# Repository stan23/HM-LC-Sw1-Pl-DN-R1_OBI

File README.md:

# HM-LC-Sw1-Pl-DN-R1_OBI          

Umbau [OBI-Wifi-Stecker](https://www.obi.de/hausfunksteuerung/wifi-stecker-schuko/p/2291706) zu HM-LC-Sw1-Pl-DN-R1_OBI

Dies basiert auf der hervorragenden Arbeit von [pa-pa](https://github.com/pa-pa/AskSinPP),  [Jérôme](https://github.com/jp112sdl/Beispiel_AskSinPP) und micha68.

# Hardware

### Bauteile

#### Reichelt

[Bestellliste](https://www.reichelt.de/my/1496083)

Bauteil                  | Bestellnummer   | Anzahl | Kommentar
------------------------ | --------------- | ------ | ---------
C6                       | X5R-G0603 10/6  |   1    | -
C1, C2, C3, C8           | X7R-G0603 100N  |   4    | -
R1                       | RND 0603 1 10K  |   1    | -
U1                       | ATMEGA 328P-AU  |   1    | -
Verbinder zu U2          | SL 1X20G 2,00   |   1    | optional, hilfreich zum Anschließen des ISP
Verbinder zu U2          | MPE 156-1-032   |   1    | optional

#### Sonstiges

Bauteil | Bestellnummer            | Anzahl | Kommentar
------- | ------------------------ | ------ | ---------
U2      | CC1101 Funkmodul 868 MHz |   1    | z.B. [eBay](https://www.ebay.de/itm/272455136087)

~8,3 cm Draht als Antenne

### Programmieradapter
- 1x ISP (um den Bootloader zu brennen, z.B. [diesen hier](https://www.diamex.de/dxshop/USB-ISP-Programmer-fuer-Atmel-AVR-Rev2))
- 1x FTDI Adapter (z.B. [Amazon](https://www.amazon.de/FT232RL-FTDI-USB-auf-TTL-Serienadapter-Arduino/dp/B00HSXDGOE))

# Software

### Fuses
Ext:  0xFF
High: 0xD2
Low:  0xE2

`C:\Program Files (x86)\Arduino\hardware\tools\avr\bin> .\avrdude -C ..\etc\avrdude.conf -p m328p -P com7 -c stk500v2 -U lfuse:w:0xE2:m -U hfuse:w:0xD2:m -U efuse:w:0xFF:m`

### Bootloader

Aus der Arduino IDE, für ATmega328P (3,3 V, 8 MHz):

`C:\Program Files (x86)\Arduino\hardware\tools\avr\bin> .\avrdude -C ..\etc\avrdude.conf -p m328p -P com7 -c stk500v2 -U flash:w:..\..\..\arduino\avr\bootloaders\atmega\ATmegaBOOT_168_atmega328_pro_8MHz.hex`

### Firmware

https://github.com/jp112sdl/Beispiel_AskSinPP/tree/master/examples/HM-LC-Sw1-Pl-DN-R1_OBI

Benötigt wird die AskSinPP aus dem master-Branch, der V3-Branch ist zu alt.

# Bauanleitung

Zuerst den ATmega auflöten, die Markierung (kleiner Punkt) muss zur Beschriftung U1 zeigen.
Danach die Kondensatoren und den Widerstand auflöten.

Mit einem Multimeter messen ob kein Kurzschluss zwischen VCC und GND besteht (mehrere 10 K Widerstand sind okay).

Den ISP Programmieradapter an die Lötaugen des CC1101 anschließen. Ein Adapterkabel vom 6-poligen ISP-Adapter auf eine 2 mm-Stiftleiste wird empfohlen :)

Pin am ISP-Kabel | Bedeutung
---------------- | ----------
1                | MISO
2                | VCC
3                | SCK
4                | MOSI
5                | Reset
6                | GND

Über den ISP den Bootloader (ATmegaBOOT_168_atmega328_pro_8MHz.hex) der mit der Arduino IDE mitgeliefert wird, brennen und die Fuses setzen. Dabei muss die Platine mit 3,3 V oder 5 V versorgt werden, entweder vom ISP oder vom FTDI-Adapter. So lange das CC1101 nicht bestückt ist, sind 5 V kein Problem.

*Achtung*: nicht die default Fuses der Arduino IDE brennen, sonst startet der ATmega nicht mehr weil er einen externen Oszillator erwartet!

Danach den FTDI USB-seriell-Adapter an die 2,54 mm-Stiftleiste stecken und mit der Arduino IDE den Sketch flashen.

Anschließend kann das Funkmodul auf der Rückseite aufgelötet werden. Dabei gibt es verschiedene Möglichkeiten:
- mit Stift- und Buchsenleiste (abnehmbar)
- mit Stiftleiste
- flach auf die SMD-Pads, hier empfiehlt es sich die Lötaugen des CC1101 zur Hälfte abzufeilen

An den Antennenanschluss muss noch das 8,3 cm Drahtstück angelötet werden.

Jetzt wieder den FTDI USB-seriell-Adapter an die 2,54 mm-Stiftleiste stecken und mit einem Terminalprogramm die Ausgabe beobachten. Es sollten schon *Ignore...*-Meldungen empfangen und angezeigt werden.

Als nächstes muss das überflüssige WLAN-Modul aus dem OBI-Stecker ausgelötet und die neue Platine eingelötet werden. Der Antennendraht muss mit Heißkleber im Gehäuse befestigt werden, so dass er möglichst weit von 230 V entfernt ist!

Nach dem Zusammenbau kann der Anlernvorgang durch langes Drücken der einzigen Taste gestartet werden. Die Anlernprozedur wird durch langsames Blinken der blauen WLAN-LED angezeigt, der Erfolg durch schnelles Blinken.

# Bilder

Dieses Werk ist lizenziert unter einer [Creative Commons Namensnennung - Nicht-kommerziell - Weitergabe unter gleichen Bedingungen 4.0 International Lizenz](http://creativecommons.org/licenses/by-nc-sa/4.0/).

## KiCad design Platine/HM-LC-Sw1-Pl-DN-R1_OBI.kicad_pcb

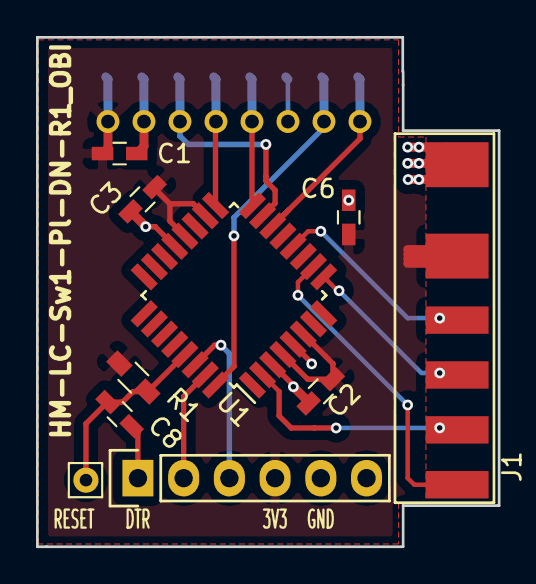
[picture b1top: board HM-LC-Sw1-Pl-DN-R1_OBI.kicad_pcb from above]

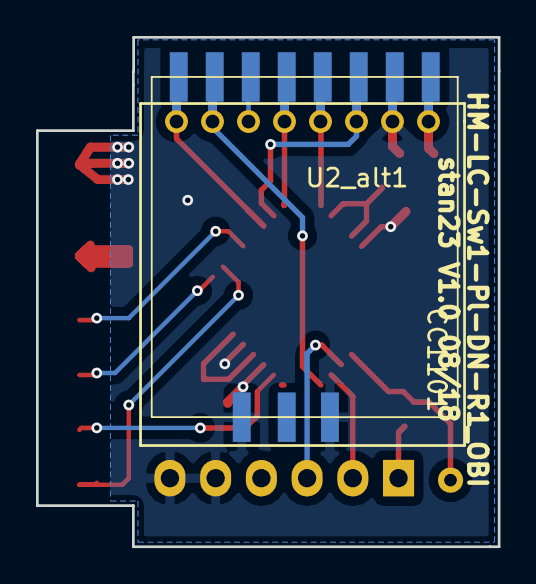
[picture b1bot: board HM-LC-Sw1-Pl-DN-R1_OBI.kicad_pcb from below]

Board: 2 copper layers, 25.7 x 28.3 mm, 12 parts (2 on the bottom side), 16 nets.

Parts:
C1, C2, C3, C8: 100n; C_0603_HandSoldering
C6: 10u; C_0603_HandSoldering
J1: Conn_OBI; OBI_Wifi_Connector
J2: FTDI; Pin_Header_Straight_1x06
J4: Reset; Pin_d0.7mm_L6.5mm_W1.8mm_FlatFork
R1: 10k; R_0603_HandSoldering
U1: ATMEGA328P-AU; TQFP-32_7x7mm_Pitch0.8mm
U2: CC1101; CC1101_Module
U2_alt1: CC1101; CC1101_SMD

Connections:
/B0: J1.4, U1.12
/D4: J1.2, U1.2
/D5: J1.3, U1.9
/D6: J1.1, U1.10
/DTR: C8.1, J2.1
/MISO: U1.16, U2.5, U2_alt1.5
/MOSI: U1.15, U2.3, U2_alt1.3
/RXD: J2.3, U1.30
/Reset: C8.2, J4.1, R1.2, U1.29
/SCK: U1.17, U2.4, U2_alt1.4
/TXD: J2.2, U1.31
GND: C1.2, C2.2, C3.2, C6.2, J1.6, J2.5, J2.6, U1.3, U1.5, U1.21, U2.2, U2_alt1.2, U2_alt1.10, U2_alt1.11
unnamed: U1.14, U2.8, U2_alt1.8
unnamed: U1.32, U2.7, U2_alt1.7
unnamed: U2.6, U2_alt1.6
VCC: C1.1, C2.1, C3.1, C6.1, J1.5, J2.4, R1.1, U1.4, U1.6, U1.18, U1.20, U2.1, U2_alt1.1

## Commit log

2018-08-12 add schematic PDF
2018-08-12 add board PDFs
2018-08-12 create directory
2018-08-12 add KiCad files
2018-08-12 add libs
2018-08-12 add board picture
2018-08-24 add pictures of the mounted PCB
2018-08-24 add pictuers to README.md
2018-08-25 add Gerber files
2018-08-26 add detailed explanation
2018-09-01 add details for avrdude
2018-09-02 add license link

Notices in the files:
README.md:
License: CC BY-NC-SA 4.0
Creative Commons Lizenzvertrag
